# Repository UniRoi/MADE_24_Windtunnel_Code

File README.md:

# MADE_24_Windtunnel_Code
## Repository for the MADE course at Reykjavik University (RU)
This repository provides resources for the Precision Machine Design course taught in the fall semester of 2024 at Reykjavik University.    
It supports project organization, code structure, and documentation for wind tunnel simulations and data analysis.

## Overview
The MADE_24_Windtunnel_Code repository offers:

### DOCS:
Datasheets, images and project raw data

### Windtunnel_Code:
This folder holds the main code for controlling and operating the wind tunnel system in the `src` and `include` folder.  
Platform IO was used for the development and the library versions are specified in the `platform.ini` file. If this project is compiled for the first time, platform IO will automatically download the necessary libraries and install them on the system.  

The `src_old` folder contains different stages of the project's development:
- `main_calib.cpp`: Initial calibration file from the HX711_ADC library.
- `main_calib_new.cpp`: Modified calibration file from the HX711_ADC library.
- `main_2loadcells.cpp`: First working code for the two-axis load cell
- `main.cpp`: First tests with the LCD.

### Windtunnel_General_Calculations:
Includes general calculation tools, along with pictures and schematics, for analyzing wind tunnel data.  

There are two subfolders in this folder, each requires a virtual pyhton environment to run the jupyter notebook file. Once the environment is created the necessary packages need to be installed with this comand: `pip install -r requirements.txt`
Each folder contains it's own `requirements.txt` file.

#### Evaluating Test Results
Multiple Jupyther notebooks to evaluate the raw data in the `Docs` folder. 

#### Platform Angular Adjustment
Jupyter notebook to calculate the platform angle for different configuration of the linkage.  

### Windtunnel_Schematic:

KICAD 8.0 was used to draw the schematic for the measurement system. This repository also includes a 3D model of the PCB and the libraries for the XFW-HX711 module.

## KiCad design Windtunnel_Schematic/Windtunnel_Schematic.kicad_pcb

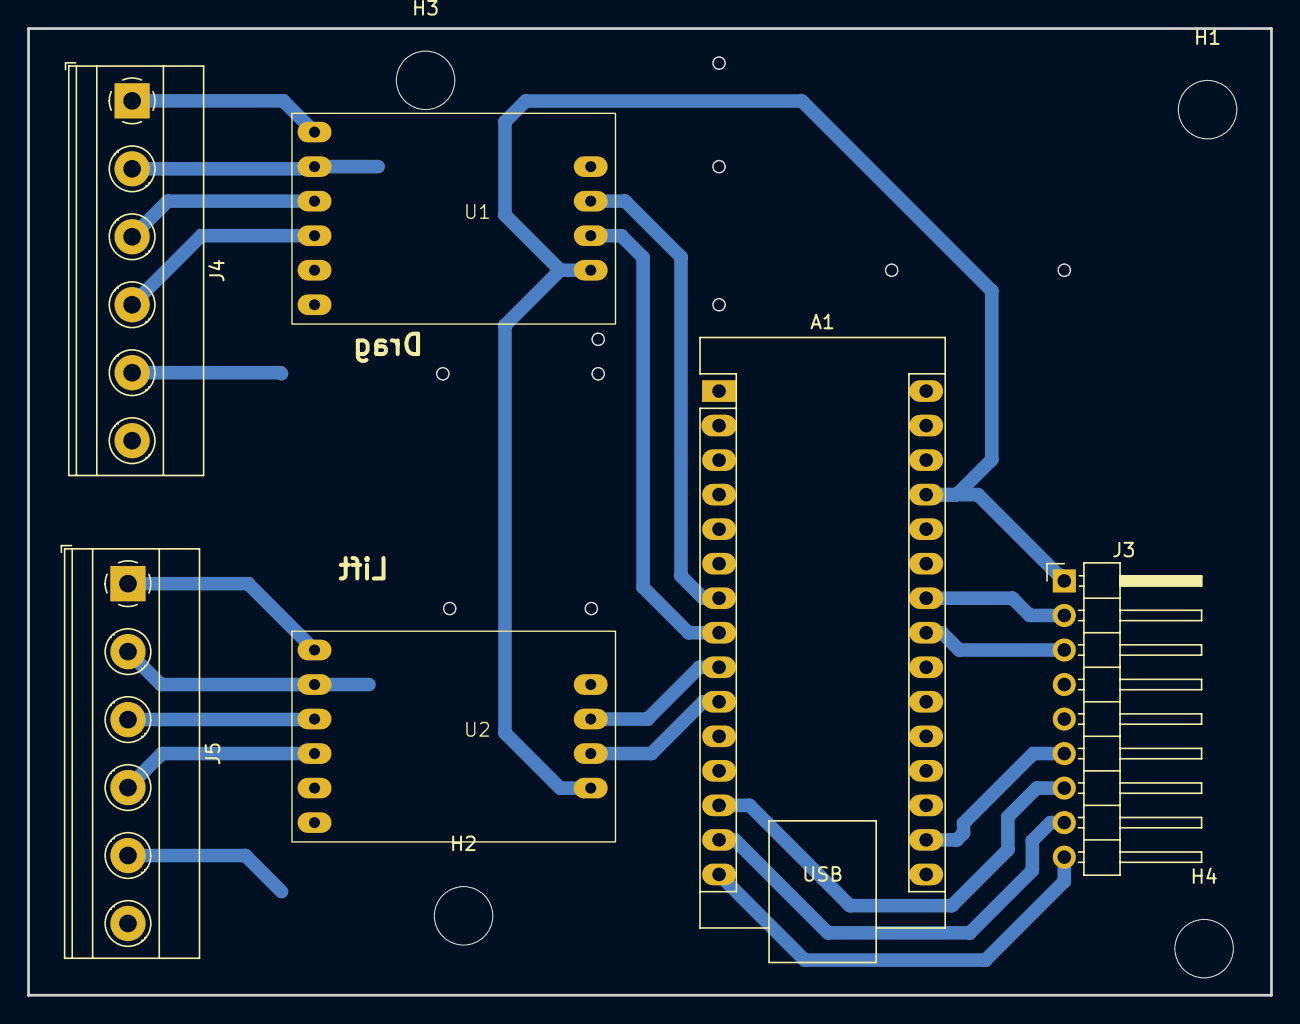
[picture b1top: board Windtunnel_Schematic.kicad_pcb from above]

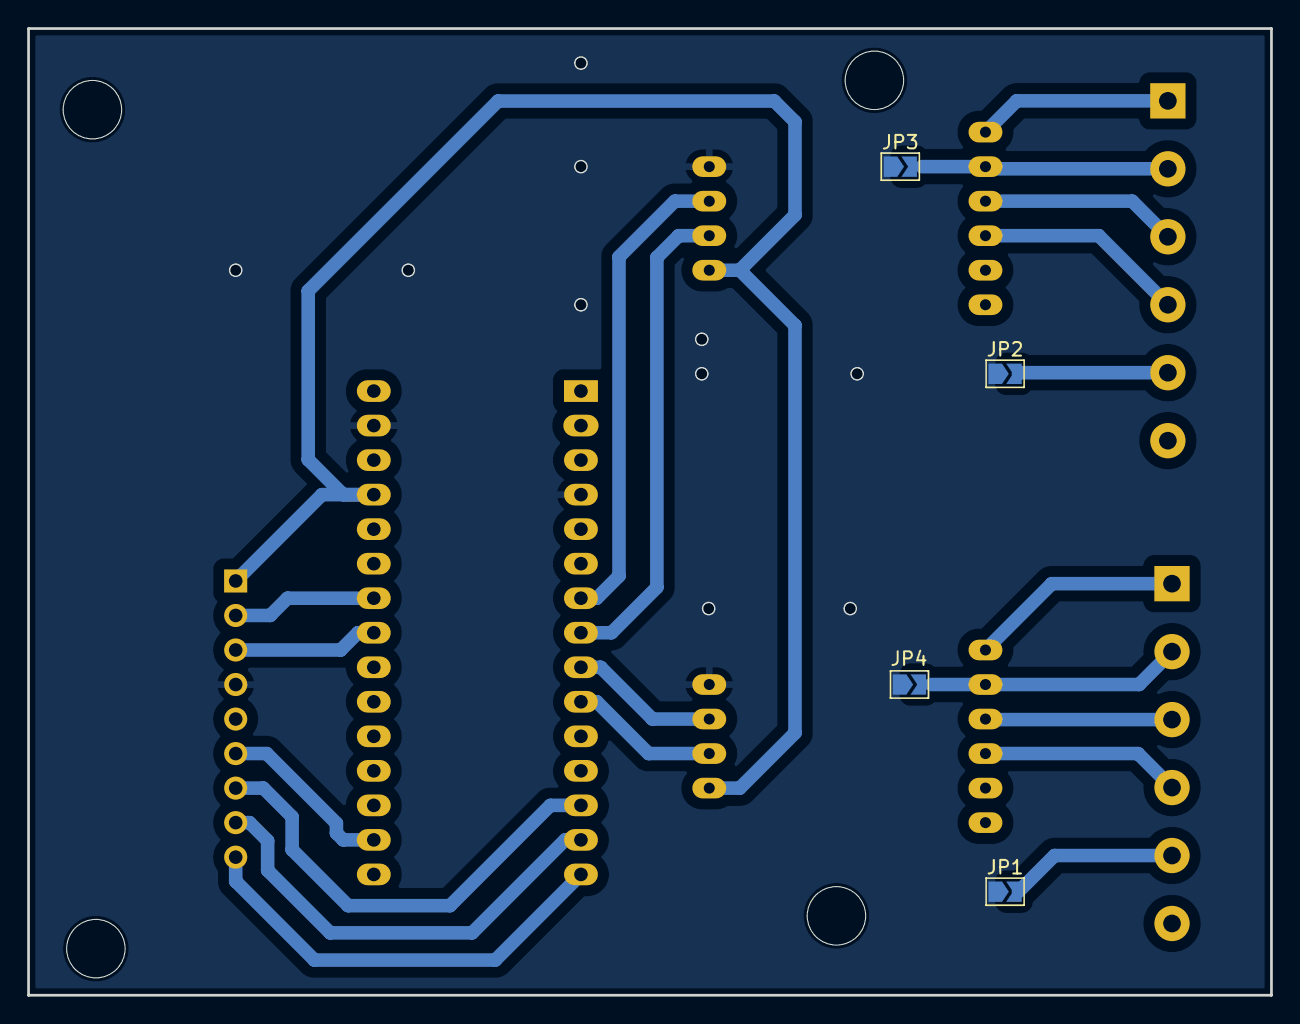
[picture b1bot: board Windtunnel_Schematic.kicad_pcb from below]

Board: 2 copper layers, 91.4 x 71.1 mm, 14 parts (4 on the bottom side), 22 nets.

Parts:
A1: Arduino_Nano_v3.x; Arduino_Nano
H1, H2, H3, H4: MountingHole; MountingHole_4.3mm_M4
J3: Conn_01x09; PinHeader_1x09_P2.54mm_Horizontal
J4, J5: Screw_Terminal_01x06; TerminalBlock_Phoenix_MKDS-1,5-6_1x06_P5.00mm_Horizontal
JP1, JP2, JP3, JP4: SolderJumper_2_Open; SolderJumper-2_P1.3mm_Open_TrianglePad1.0x1.5mm
U1, U2: xfw_hx711

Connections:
+3.3V: A1.17 (3V3), J3.6
+5V: A1.27 (+5V), J3.1, U1.10 (VCC), U2.10 (VCC)
/Arduino_nano/A4_SDA: A1.23 (A4), J3.3
/Arduino_nano/A5_SCL: A1.24 (A5), J3.2
/Arduino_nano/D4_DOUT_L2: A1.7 (D4), U1.8 (DOUT)
/Arduino_nano/D5_SCK_L2: A1.8 (D5), U1.9 (SCK)
/Arduino_nano/D6_DOUT_L1: A1.9 (D6), U2.8 (DOUT)
/Arduino_nano/D7_SCK_L1: A1.10 (D7), U2.9 (SCK)
/Arduino_nano/D11: A1.13 (D10), J3.7
/Arduino_nano/D12: A1.14 (D11), J3.8
/Arduino_nano/D13: A1.15 (D12), J3.9
/HX711/A+: J4.4, U1.4 (A+)
/HX711/A-: J4.3, U1.3 (A-)
/HX711/E+: J4.1, U1.1 (E+)
/HX711/E-: J4.2, JP3.2 (B), U1.2 (E-)
/HX712/A+: J5.4, U2.4 (A+)
/HX712/A-: J5.3, U2.3 (A-)
/HX712/E+: J5.1, U2.1 (E+)
/HX712/E-: J5.2, JP4.2 (B), U2.2 (E-)
GND: A1.4 (GND), A1.29 (GND), J3.4, JP1.1 (A), JP2.1 (A), JP3.1 (A), JP4.1 (A), U1.7 (GND), U2.7 (GND)
unnamed: J4.5, JP2.2 (B)
unnamed: J5.5, JP1.2 (B)

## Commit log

2024-09-27 Testing hx711 lib ADD lib dep CHANGE main to lib testing example
2024-09-28 Tests: ADD monitor speed info ADD liquid crystal lib
2024-09-28 Test calibration Test calibration example
2024-09-28 Test with eeprom Tested readings with calibration value read from eeprom Works :)
2024-10-03 Test 2-axis loadcell Used example code from library
2024-10-08 Add folder for basic calculations ADD: jupyter notebook for calculating the platform angle
2024-10-12 Linear angle: CHANGED: played with differnet lengths for the linkage
2024-10-23 Linearisation: ADD: linear slope values ADD: function with solver to solve the leadscrew length for a given angle
2024-10-23 Linearisation: Add: linearization
2024-10-26 First Version Add: version control Add: button handling with debounce time Add: conversion to newton Add: Display driver
2024-10-26 First draft of schematic MISSING: plug for connecting the button and display to the controll board
2024-10-29 Added sub D9 and screw terminals
2024-10-31 Add Calibration values
2024-10-31 Schematic to 0.3.0 Nearly finished Trying to mill it tomorrow
2024-10-31 Code: Add new calibration tool to get also the offset value for each loadcell
2024-11-01 Schematic: First version is done and working TODO: Add labling to pcb Add comments Add changes for next version, but we will not manufacture this one
2024-11-01 Change pins in the code because the routing was easier this way
2024-11-01 Schematic: add step file for pcb to make the housing
2024-11-03 Add arduino step file
2024-11-03 3D model contains not the arduino
2024-11-07 Change length of plattform
2024-11-07 Add data evaluation scripts and image folder
2024-11-07 Add raw data
2024-11-11 Pictures, schematic, and evaluation scripts for data - ADD: Schematic pdf and png - ADD: Pictures for presentation - CHANGE: evaluation scripts to show right data output - ADD: xlsx for angle over ro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
2024-11-14 Add to docs, schematic and general calculation: ADD prototype data Change Schematic revision to 0.4.0 ADD requirements.txt for each general calculation virtual environment
2024-11-14 Update Readme and add schematic pdf
2024-11-14 Add Manufacturing files for pcb
2024-11-14 Matlab lift and drag calculations
2024-11-14 Matlab angle analysis upload
2024-11-14 Information content code upload
2024-11-20 Split two axis evaluation image in four single images
2024-11-20 AAR analysis for resubmission
2024-11-20 ANOVA
    ANOVA for table 4
2024-11-22 Add cells for independent figures
